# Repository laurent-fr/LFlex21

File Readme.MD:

# LFlex21, a single board 6809/Flex computer

   * 6809 CPU
   * 58Kb RAM
   * 4Kb ROM
   * 2Kb NVRAM
   * RTC clock
   * Serial interface up to 9600 bauds
   * Centronic printer port
   * floppy controller
   * FLEX09 operating system

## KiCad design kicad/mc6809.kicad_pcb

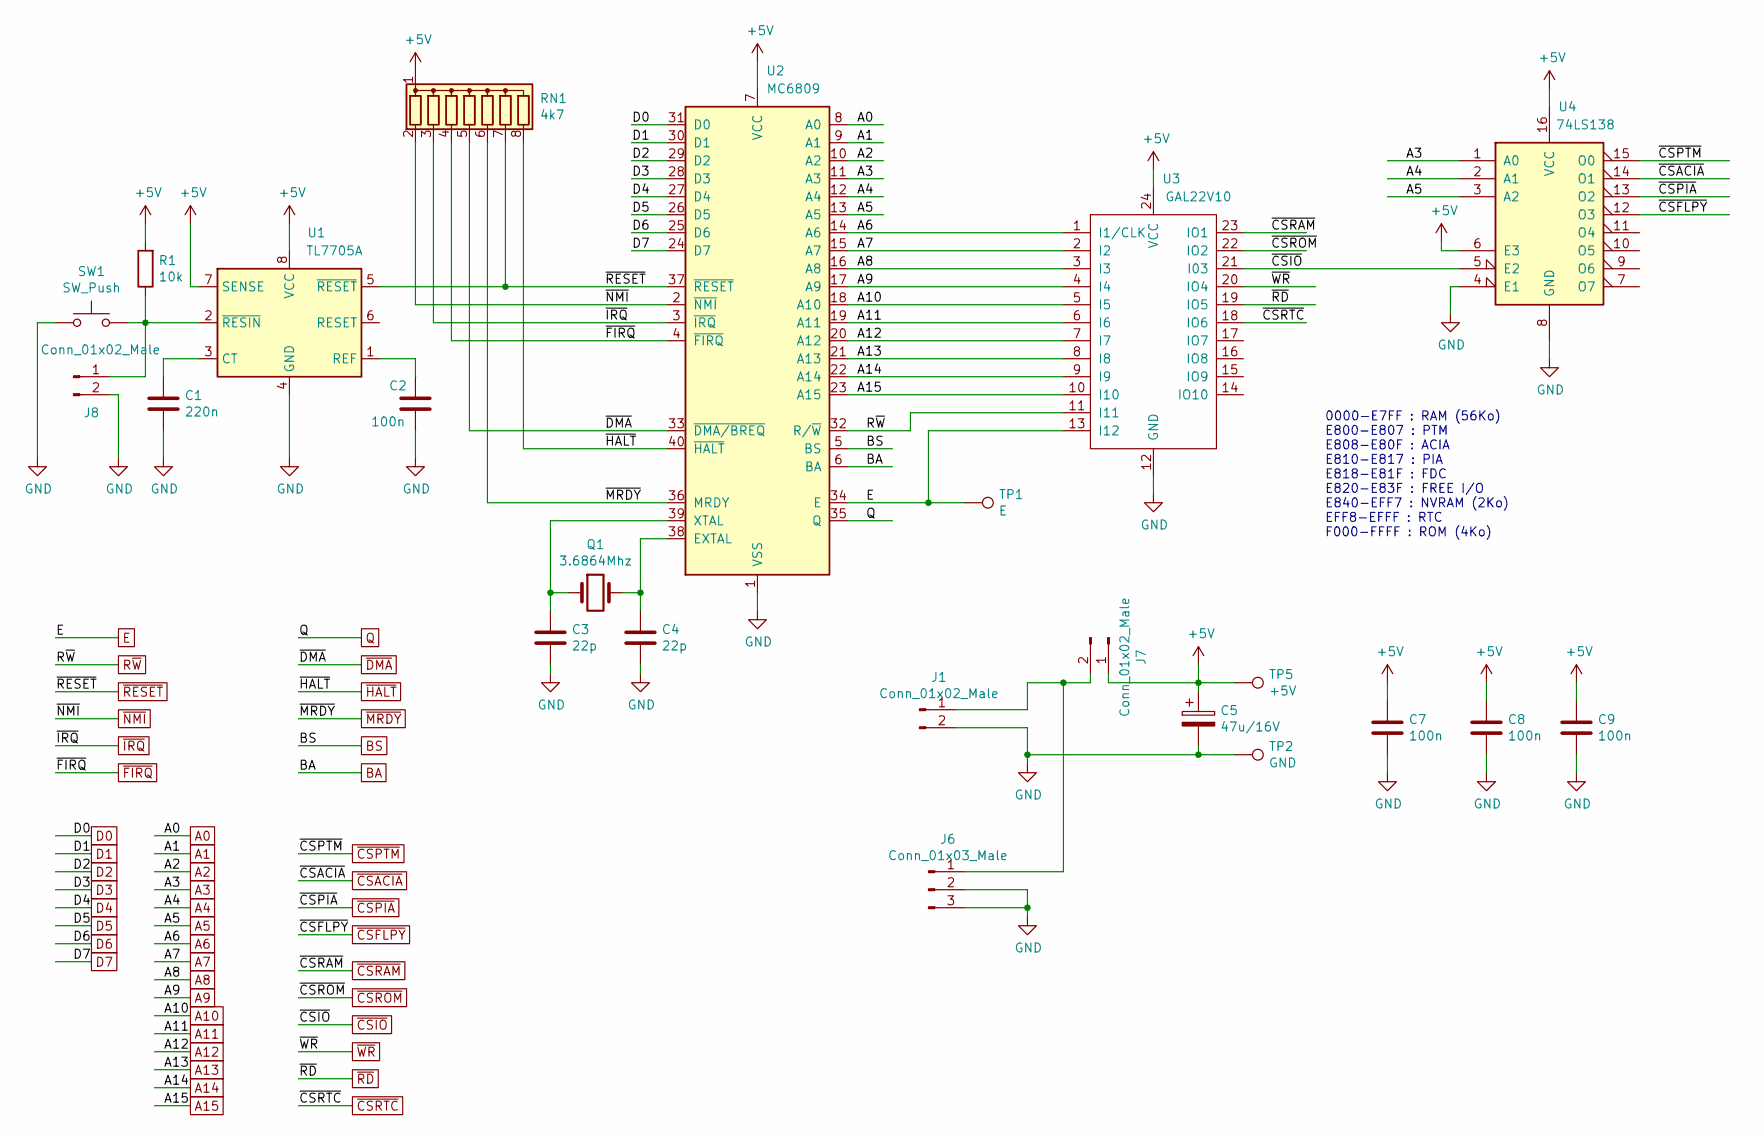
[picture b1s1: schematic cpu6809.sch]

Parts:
C1: 220n; C_Disc_D4.3mm_W1.9mm_P5.00mm
C2, C7, C8, C9: 100n; C_Disc_D4.3mm_W1.9mm_P5.00mm
C3, C4: 22p; C_Disc_D3.0mm_W1.6mm_P2.50mm
C5: 47u/16V; CP_Radial_D5.0mm_P2.50mm
J1: Conn_01x02_Male; JACK_ALIM
J6: Conn_01x03_Male; Molex_KK-6410-03_03x2.54mm_Straight
J7: Conn_01x02_Male; Molex_KK-6410-02_02x2.54mm_Straight
J8: Conn_01x02_Male; Pin_Header_Straight_1x02_Pitch2.54mm
Q1: 3.6864Mhz; Crystal_HC18-U_Vertical
R1: 10k; R_Axial_DIN0207_L6.3mm_D2.5mm_P7.62mm_Horizontal
RN1: 4k7; R_Array_SIP8
SW1: SW_Push; SW_PUSH_6mm
TP1: E; Pin_d1.0mm_L10.0mm
TP2: GND; Pin_d1.0mm_L10.0mm
TP5: +5V; Pin_d1.0mm_L10.0mm
U1: TL7705A; DIP-8_W7.62mm_LongPads
U2: MC6809; DIP-40_W15.24mm_LongPads
U3: GAL22V10; DIP-24_W7.62mm_LongPads
U4: 74LS138; DIP-16_W7.62mm_LongPads

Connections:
+5V: C5.1, C7.1, C8.1, C9.1, J7.1, R1.2, RN1.1 (common), TP5.1, U1.7 (SENSE), U1.8 (VCC), U2.7 (VCC), U3.24 (VCC), U4.6 (E3), U4.16 (VCC); also elsewhere on the board
A0: U2.8 (A0); also elsewhere on the board
A1: U2.9 (A1); also elsewhere on the board
A2: U2.10 (A2); also elsewhere on the board
A3: U2.11 (A3), U4.1 (A0); also elsewhere on the board
A4: U2.12 (A4), U4.2 (A1); also elsewhere on the board
A5: U2.13 (A5), U4.3 (A2); also elsewhere on the board
A6: U2.14 (A6), U3.1 (I1/CLK); also elsewhere on the board
A7: U2.15 (A7), U3.2 (I2); also elsewhere on the board
A8: U2.16 (A8), U3.3 (I3); also elsewhere on the board
A9: U2.17 (A9), U3.4 (I4); also elsewhere on the board
A10: U2.18 (A10), U3.5 (I5); also elsewhere on the board
A11: U2.19 (A11), U3.6 (I6); also elsewhere on the board
A12: U2.20 (A12), U3.7 (I7); also elsewhere on the board
A13: U2.21 (A13), U3.8 (I8); also elsewhere on the board
A14: U2.22 (A14), U3.9 (I9); also elsewhere on the board
A15: U2.23 (A15), U3.10 (I10); also elsewhere on the board
BA: U2.6 (BA); also elsewhere on the board
BS: U2.5 (BS); also elsewhere on the board
D0: U2.31 (D0); also elsewhere on the board
D1: U2.30 (D1); also elsewhere on the board
D2: U2.29 (D2); also elsewhere on the board
D3: U2.28 (D3); also elsewhere on the board
D4: U2.27 (D4); also elsewhere on the board
D5: U2.26 (D5); also elsewhere on the board
D6: U2.25 (D6); also elsewhere on the board
D7: U2.24 (D7); also elsewhere on the board
E: TP1.1, U2.34 (E), U3.13 (I12); also elsewhere on the board
GND: C1.2, C2.2, C3.2, C4.2, C5.2, C7.2, C8.2, C9.2, J1.2, J6.2, J6.3, J8.2, SW1.1, TP2.1, U1.4 (GND), U2.1 (VSS), U3.12 (GND), U4.4 (E1), U4.8 (GND); also elsewhere on the board
unnamed: C1.1, U1.3 (CT)
unnamed: C2.1, U1.1 (REF)
unnamed: C3.1, Q1.1, U2.39 (XTAL)
unnamed: C4.1, Q1.2, U2.38 (EXTAL)
unnamed: J1.1, J6.1, J7.2
unnamed: J8.1, R1.1, SW1.2, U1.2 (~RESIN)
Q: U2.35 (Q); also elsewhere on the board
R~W~: U2.32 (R/~W), U3.11 (I11); also elsewhere on the board
~CSACIA~: U4.14 (O1); also elsewhere on the board
~CSFLPY~: U4.12 (O3); also elsewhere on the board
~CSIO~: U3.21 (I03), U4.5 (E2); also elsewhere on the board
~CSPIA~: U4.13 (O2); also elsewhere on the board
~CSPTM~: U4.15 (O0); also elsewhere on the board
~CSRAM~: U3.23 (IO1); also elsewhere on the board
~CSROM~: U3.22 (IO2); also elsewhere on the board
~CSRTC~: U3.18 (IO6); also elsewhere on the board
~DMA~: RN1.5 (R4), U2.33 (~DMA/BREQ); also elsewhere on the board
~FIRQ~: RN1.4 (R3), U2.4 (~FIRQ); also elsewhere on the board
~HALT~: RN1.8 (R7), U2.40 (~HALT); also elsewhere on the board
~IRQ~: RN1.3 (R2), U2.3 (~IRQ); also elsewhere on the board
~MRDY~: RN1.6 (R5), U2.36 (MRDY); also elsewhere on the board
~NMI~: RN1.2 (R1), U2.2 (~NMI); also elsewhere on the board
~RD~: U3.19 (IO5); also elsewhere on the board
~RESET~: RN1.7 (R6), U1.5 (~RESET), U2.37 (~RESET); also elsewhere on the board
~WR~: U3.20 (IO4); also elsewhere on the board

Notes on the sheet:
0000-E7FF : RAM (56Ko) E800-E807 : PTM E808-E80F : ACIA E810-E817 : PIA E818-E81F : FDC E820-E83F : FREE I/O E840-EFF7 : NVRAM (2Ko) EFF8-EFFF : RTC F000-FFFF : ROM (4Ko)

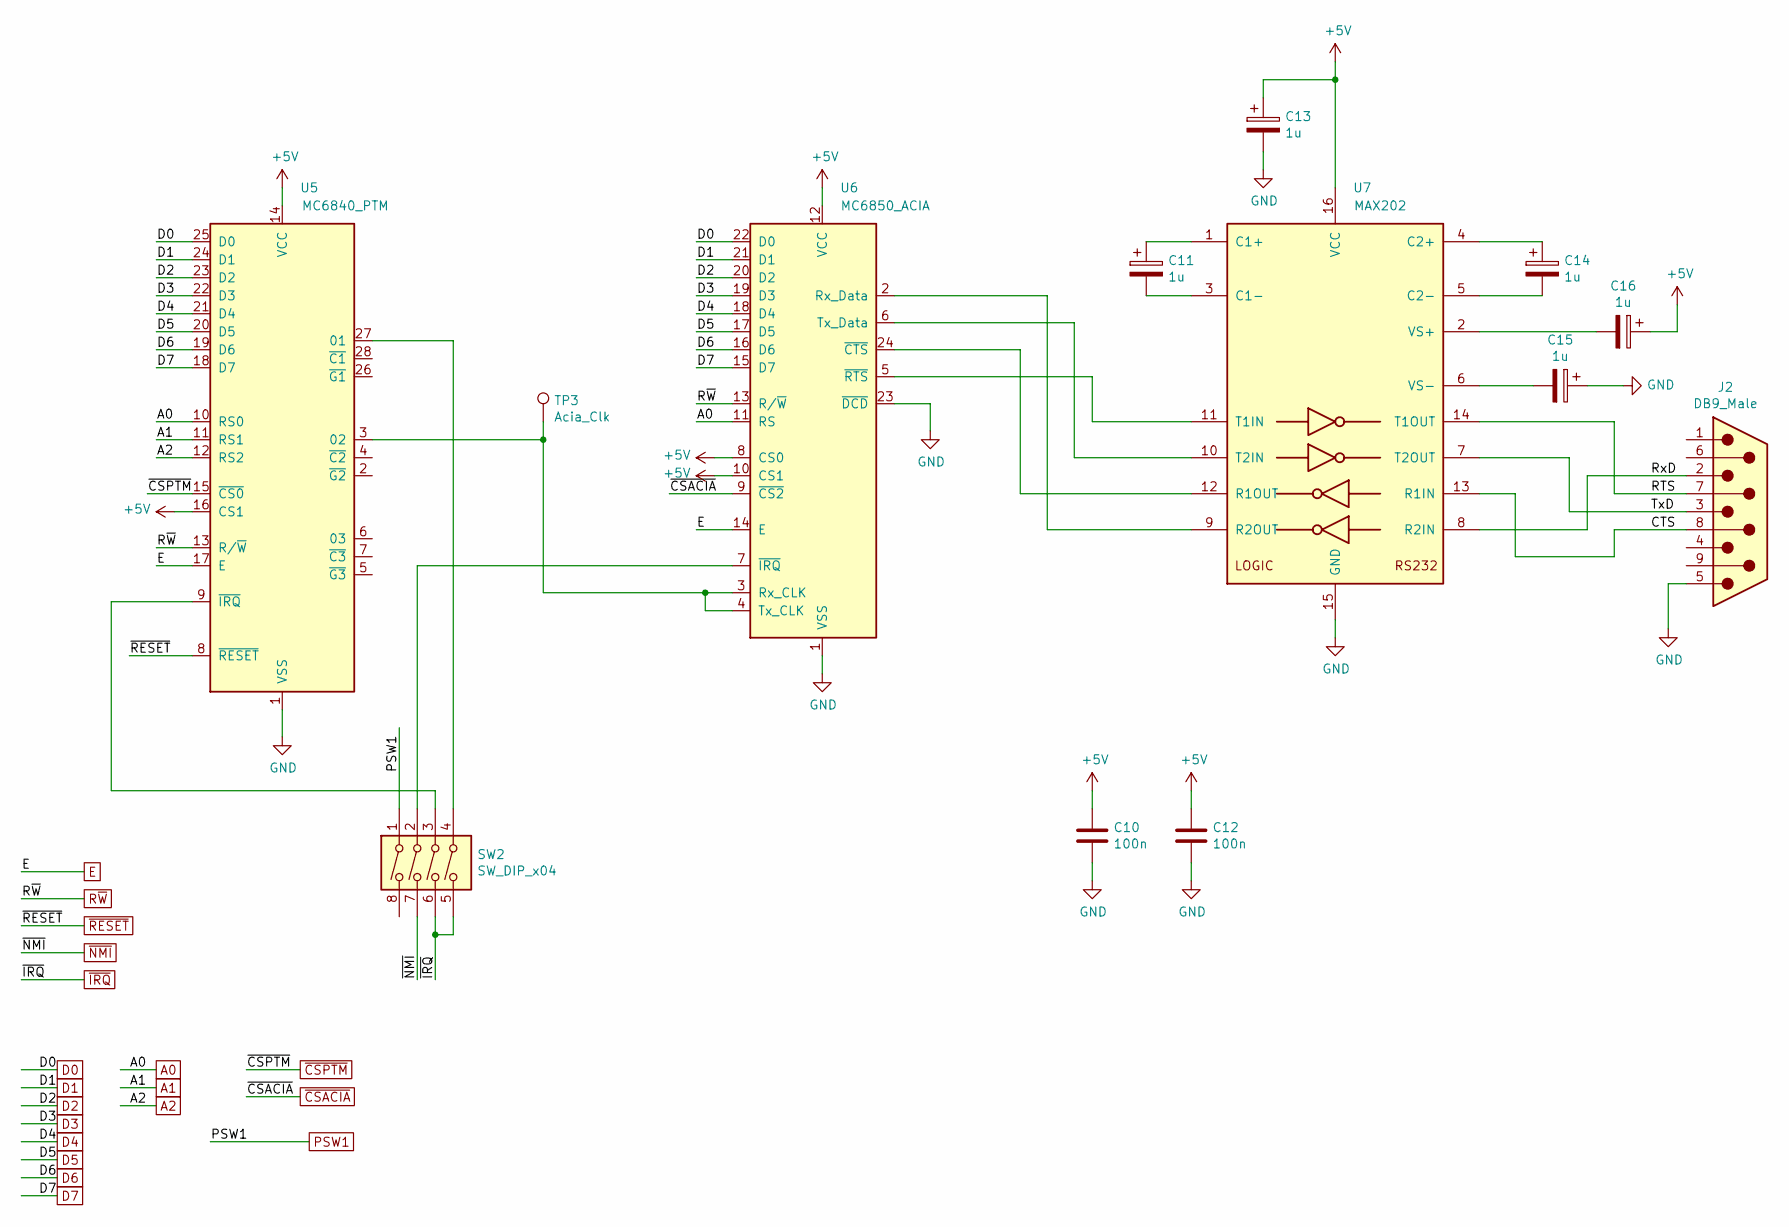
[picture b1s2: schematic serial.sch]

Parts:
C10, C12: 100n; C_Disc_D4.3mm_W1.9mm_P5.00mm
C11, C13, C14, C15, C16: 1u; CP_Radial_D5.0mm_P2.50mm
J2: DB9_Male; DSUB-9_Male_Horizontal_Pitch2.77x2.84mm_EdgePinOffset7.70mm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
SW2: SW_DIP_x04; SW_DIP_x4_W7.62mm_Slide
TP3: Acia_Clk; Pin_d1.0mm_L10.0mm
U5: MC6840_PTM; DIP-28_W15.24mm_LongPads
U6: MC6850_ACIA; DIP-24_W15.24mm_LongPads
U7: MAX202; DIP-16_W7.62mm_LongPads

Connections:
+5V: C10.1, C12.1, C13.1, C16.1, U5.14 (VCC), U5.16 (CS1), U6.8 (CS0), U6.10 (CS1), U6.12 (VCC), U7.16 (VCC); also elsewhere on the board
/serial/CTS: J2.8, U7.13 (R1IN)
/serial/RTS: J2.7, U7.14 (T1OUT)
/serial/RxD: J2.2, U7.8 (R2IN)
/serial/TxD: J2.3, U7.7 (T2OUT)
A0: U5.10 (RS0), U6.11 (RS); also elsewhere on the board
A1: U5.11 (RS1); also elsewhere on the board
A2: U5.12 (RS2); also elsewhere on the board
D0: U5.25 (D0), U6.22 (D0); also elsewhere on the board
D1: U5.24 (D1), U6.21 (D1); also elsewhere on the board
D2: U5.23 (D2), U6.20 (D2); also elsewhere on the board
D3: U5.22 (D3), U6.19 (D3); also elsewhere on the board
D4: U5.21 (D4), U6.18 (D4); also elsewhere on the board
D5: U5.20 (D5), U6.17 (D5); also elsewhere on the board
D6: U5.19 (D6), U6.16 (D6); also elsewhere on the board
D7: U5.18 (D7), U6.15 (D7); also elsewhere on the board
E: U5.17 (E), U6.14 (E); also elsewhere on the board
GND: C10.2, C12.2, C13.2, C15.1, J2.5, U5.1 (VSS), U6.1 (VSS), U6.23 (~DCD), U7.15 (GND); also elsewhere on the board
unnamed: C11.1, U7.1 (C1+)
unnamed: C11.2, U7.3 (C1-)
unnamed: C14.1, U7.4 (C2+)
unnamed: C14.2, U7.5 (C2-)
unnamed: C15.2, U7.6 (VS-)
unnamed: C16.2, U7.2 (VS+)
unnamed: SW2.2, U6.7 (~IRQ)
unnamed: SW2.3, U5.9 (~IRQ)
unnamed: SW2.4, U5.27 (01)
unnamed: TP3.1, U5.3 (02), U6.3 (Rx_CLK), U6.4 (Tx_CLK)
unnamed: U6.2 (Rx_Data), U7.9 (R2OUT)
unnamed: U6.5 (~RTS), U7.11 (T1IN)
unnamed: U6.6 (Tx_Data), U7.10 (T2IN)
unnamed: U6.24 (~CTS), U7.12 (R1OUT)
PSW1: SW2.1; also elsewhere on the board
R~W~: U5.13 (R/~W), U6.13 (R/~W); also elsewhere on the board
~CSACIA~: U6.9 (~CS2~); also elsewhere on the board
~CSPTM~: U5.15 (~CS0~); also elsewhere on the board
~IRQ~: SW2.5, SW2.6; also elsewhere on the board
~NMI~: SW2.7; also elsewhere on the board
~RESET~: U5.8 (~RESET); also elsewhere on the board

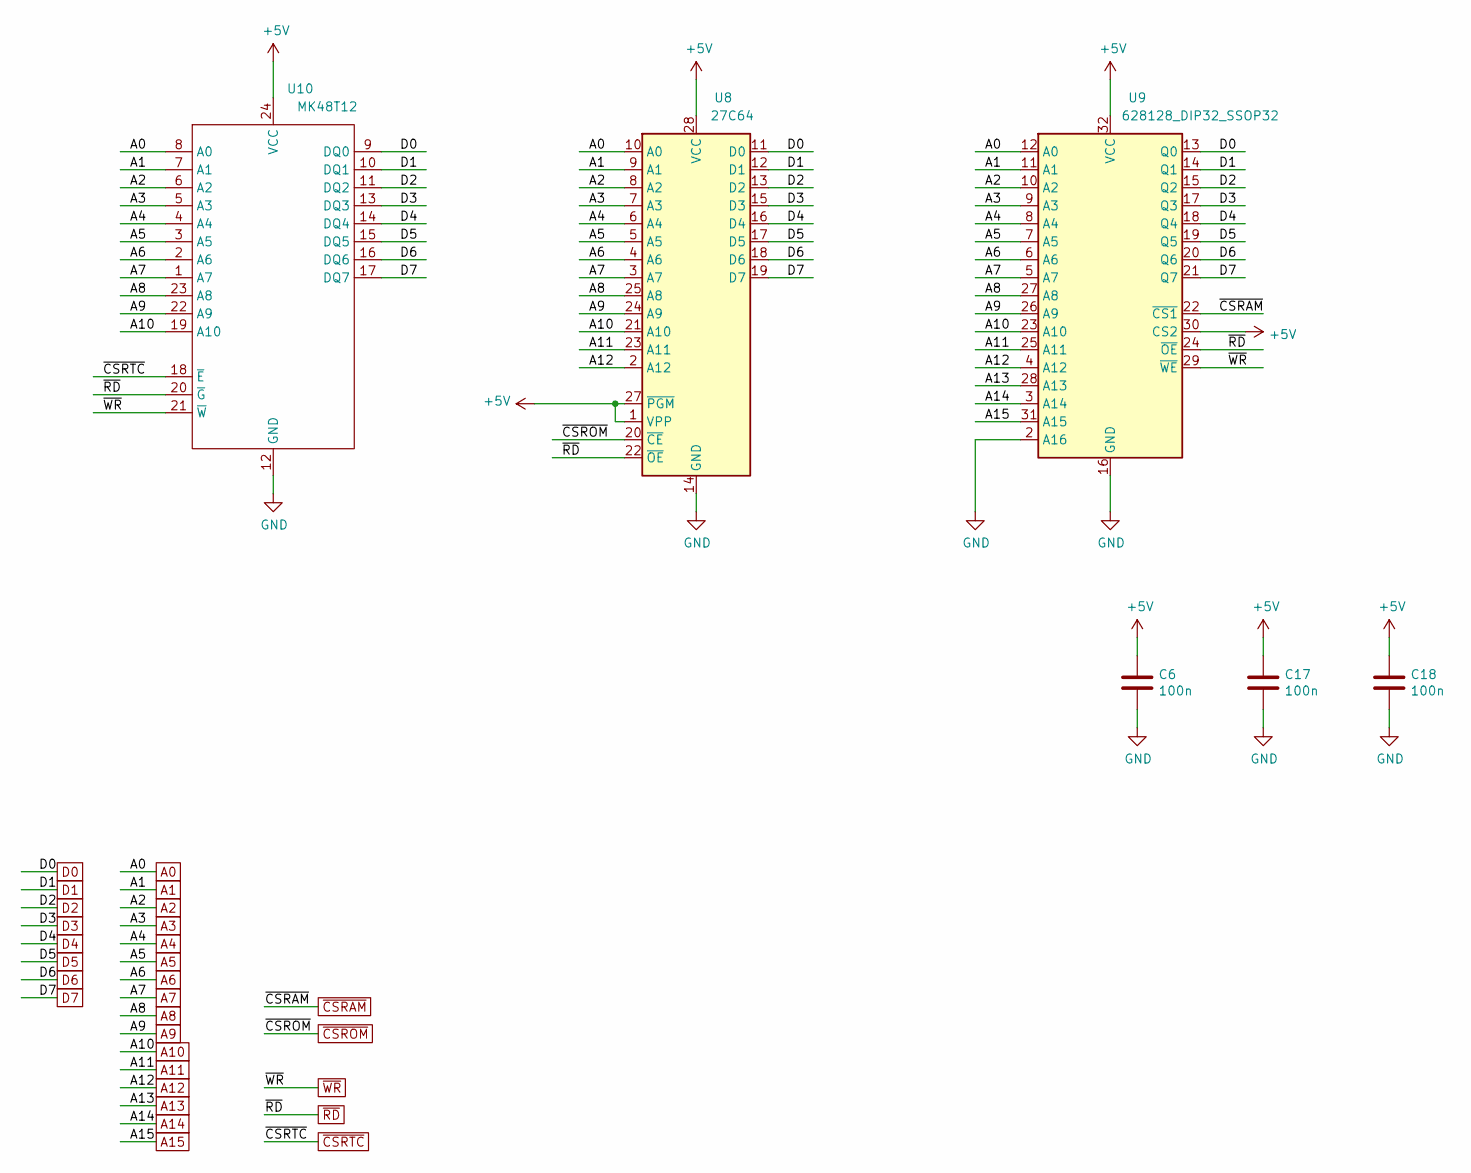
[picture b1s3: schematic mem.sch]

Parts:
C6, C17, C18: 100n; C_Disc_D4.3mm_W1.9mm_P5.00mm
U8: 27C64; DIP-28_W15.24mm_LongPads
U9: 628128_DIP32_SSOP32; DIP-32_W15.24mm_LongPads
U10: MK48T12; DIP-24_W15.24mm_LongPads

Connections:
+5V: C6.1, C17.1, C18.1, U8.1 (VPP), U8.27 (~PGM), U8.28 (VCC), U9.30 (CS2), U9.32 (VCC), U10.24 (VCC); also elsewhere on the board
A0: U8.10 (A0), U9.12 (A0), U10.8 (A0); also elsewhere on the board
A1: U8.9 (A1), U9.11 (A1), U10.7 (A1); also elsewhere on the board
A2: U8.8 (A2), U9.10 (A2), U10.6 (A2); also elsewhere on the board
A3: U8.7 (A3), U9.9 (A3), U10.5 (A3); also elsewhere on the board
A4: U8.6 (A4), U9.8 (A4), U10.4 (A4); also elsewhere on the board
A5: U8.5 (A5), U9.7 (A5), U10.3 (A5); also elsewhere on the board
A6: U8.4 (A6), U9.6 (A6), U10.2 (A6); also elsewhere on the board
A7: U8.3 (A7), U9.5 (A7), U10.1 (A7); also elsewhere on the board
A8: U8.25 (A8), U9.27 (A8), U10.23 (A8); also elsewhere on the board
A9: U8.24 (A9), U9.26 (A9), U10.22 (A9); also elsewhere on the board
A10: U8.21 (A10), U9.23 (A10), U10.19 (A10); also elsewhere on the board
A11: U8.23 (A11), U9.25 (A11); also elsewhere on the board
A12: U8.2 (A12), U9.4 (A12); also elsewhere on the board
A13: U9.28 (A13); also elsewhere on the board
A14: U9.3 (A14); also elsewhere on the board
A15: U9.31 (A15); also elsewhere on the board
D0: U8.11 (D0), U9.13 (Q0), U10.9 (DQ0); also elsewhere on the board
D1: U8.12 (D1), U9.14 (Q1), U10.10 (DQ1); also elsewhere on the board
D2: U8.13 (D2), U9.15 (Q2), U10.11 (DQ2); also elsewhere on the board
D3: U8.15 (D3), U9.17 (Q3), U10.13 (DQ3); also elsewhere on the board
D4: U8.16 (D4), U9.18 (Q4), U10.14 (DQ4); also elsewhere on the board
D5: U8.17 (D5), U9.19 (Q5), U10.15 (DQ5); also elsewhere on the board
D6: U8.18 (D6), U9.20 (Q6), U10.16 (DQ6); also elsewhere on the board
D7: U8.19 (D7), U9.21 (Q7), U10.17 (DQ7); also elsewhere on the board
GND: C6.2, C17.2, C18.2, U8.14 (GND), U9.2 (A16), U9.16 (GND), U10.12 (GND); also elsewhere on the board
~CSRAM~: U9.22 (~CS1); also elsewhere on the board
~CSROM~: U8.20 (~CE); also elsewhere on the board
~CSRTC~: U10.18 (~E~); also elsewhere on the board
~RD~: U8.22 (~OE), U9.24 (~OE), U10.20 (~G~); also elsewhere on the board
~WR~: U9.29 (~WE), U10.21 (~W~); also elsewhere on the board

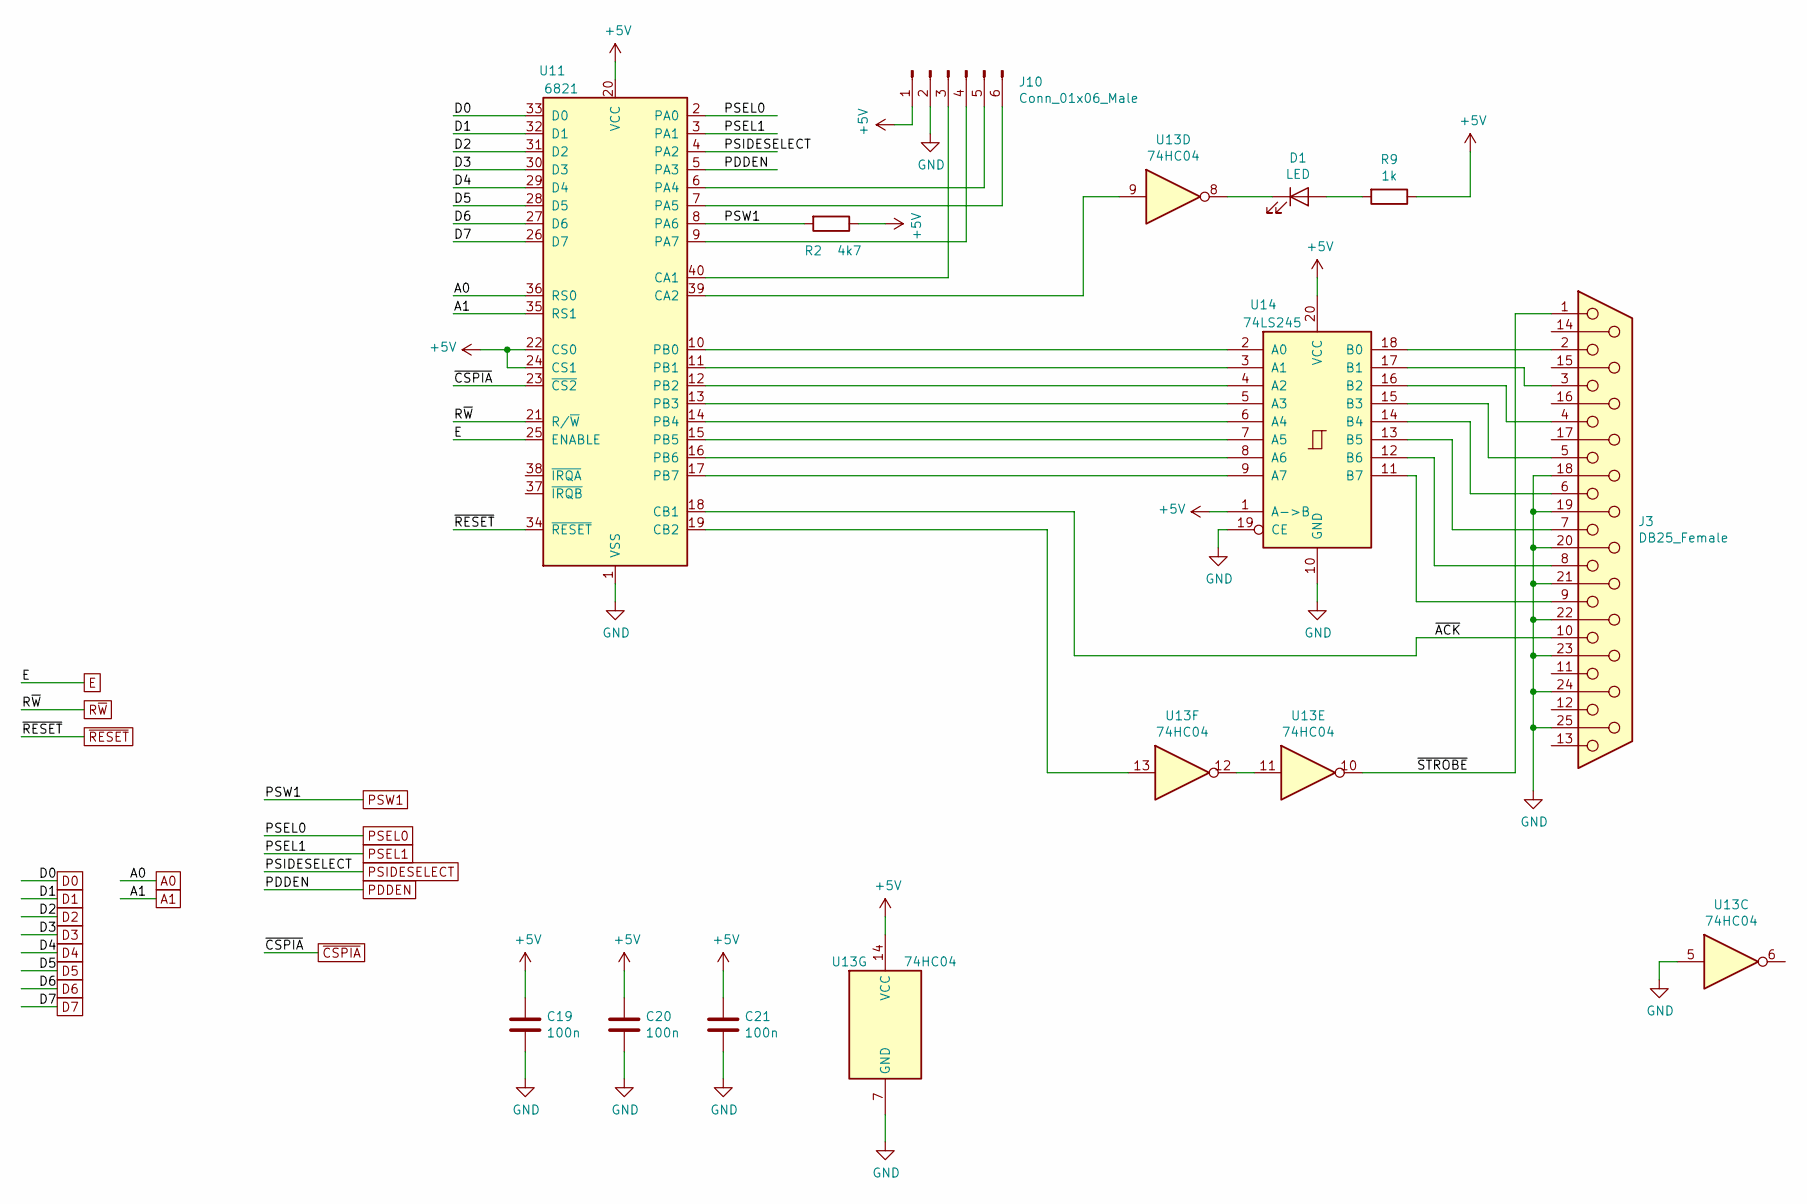
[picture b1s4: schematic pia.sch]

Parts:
C19, C20, C21: 100n; C_Disc_D4.3mm_W1.9mm_P5.00mm
D1: LED; LED_D3.0mm
J3: DB25_Female; DSUB-25_Female_Horizontal_Pitch2.77x2.84mm_EdgePinOffset7.7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
J10: Conn_01x06_Male; Pin_Header_Straight_1x06_Pitch2.54mm
R2: 4k7; R_Axial_DIN0207_L6.3mm_D2.5mm_P7.62mm_Horizontal
R9: 1k; R_Axial_DIN0207_L6.3mm_D2.5mm_P7.62mm_Horizontal
U11: 6821; DIP-40_W15.24mm_LongPads
U13: 74HC04; DIP-14_W7.62mm_LongPads
U14: 74LS245; DIP-20_W7.62mm_LongPads

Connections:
+5V: C19.1, C20.1, C21.1, J10.1, R2.1, R9.1, U11.20 (VCC), U11.22 (CS0), U11.24 (CS1), U13.14 (VCC), U14.1 (A->B), U14.20 (VCC); also elsewhere on the board
/pia/~ACK~: J3.10, U11.18 (CB1)
/pia/~STROBE~: J3.1, U13.10
A0: U11.36 (RS0); also elsewhere on the board
A1: U11.35 (RS1); also elsewhere on the board
D0: U11.33 (D0); also elsewhere on the board
D1: U11.32 (D1); also elsewhere on the board
D2: U11.31 (D2); also elsewhere on the board
D3: U11.30 (D3); also elsewhere on the board
D4: U11.29 (D4); also elsewhere on the board
D5: U11.28 (D5); also elsewhere on the board
D6: U11.27 (D6); also elsewhere on the board
D7: U11.26 (D7); also elsewhere on the board
E: U11.25 (ENABLE); also elsewhere on the board
GND: C19.2, C20.2, C21.2, J3.18, J3.19, J3.20, J3.21, J3.22, J3.23, J3.24, J3.25, J10.2, U11.1 (VSS), U13.5, U13.7 (GND), U14.10 (GND), U14.19 (CE); also elsewhere on the board
unnamed: D1.1 (K), U13.8
unnamed: D1.2 (A), R9.2
unnamed: J3.2, U14.18 (B0)
unnamed: J3.3, U14.17 (B1)
unnamed: J3.4, U14.16 (B2)
unnamed: J3.5, U14.15 (B3)
unnamed: J3.6, U14.14 (B4)
unnamed: J3.7, U14.13 (B5)
unnamed: J3.8, U14.12 (B6)
unnamed: J3.9, U14.11 (B7)
unnamed: J10.3, U11.40 (CA1)
unnamed: J10.4, U11.9 (PA7)
unnamed: J10.5, U11.6 (PA4)
unnamed: J10.6, U11.7 (PA5)
unnamed: U11.10 (PB0), U14.2 (A0)
unnamed: U11.11 (PB1), U14.3 (A1)
unnamed: U11.12 (PB2), U14.4 (A2)
unnamed: U11.13 (PB3), U14.5 (A3)
unnamed: U11.14 (PB4), U14.6 (A4)
unnamed: U11.15 (PB5), U14.7 (A5)
unnamed: U11.16 (PB6), U14.8 (A6)
unnamed: U11.17 (PB7), U14.9 (A7)
unnamed: U11.19 (CB2), U13.13
unnamed: U11.39 (CA2), U13.9
unnamed: U13.11, U13.12
PDDEN: U11.5 (PA3); also elsewhere on the board
PSEL0: U11.2 (PA0); also elsewhere on the board
PSEL1: U11.3 (PA1); also elsewhere on the board
PSIDESELECT: U11.4 (PA2); also elsewhere on the board
PSW1: R2.2, U11.8 (PA6); also elsewhere on the board
R~W~: U11.21 (R/~W); also elsewhere on the board
~CSPIA~: U11.23 (~CS2); also elsewhere on the board
~RESET~: U11.34 (~RESET); also elsewhere on the board

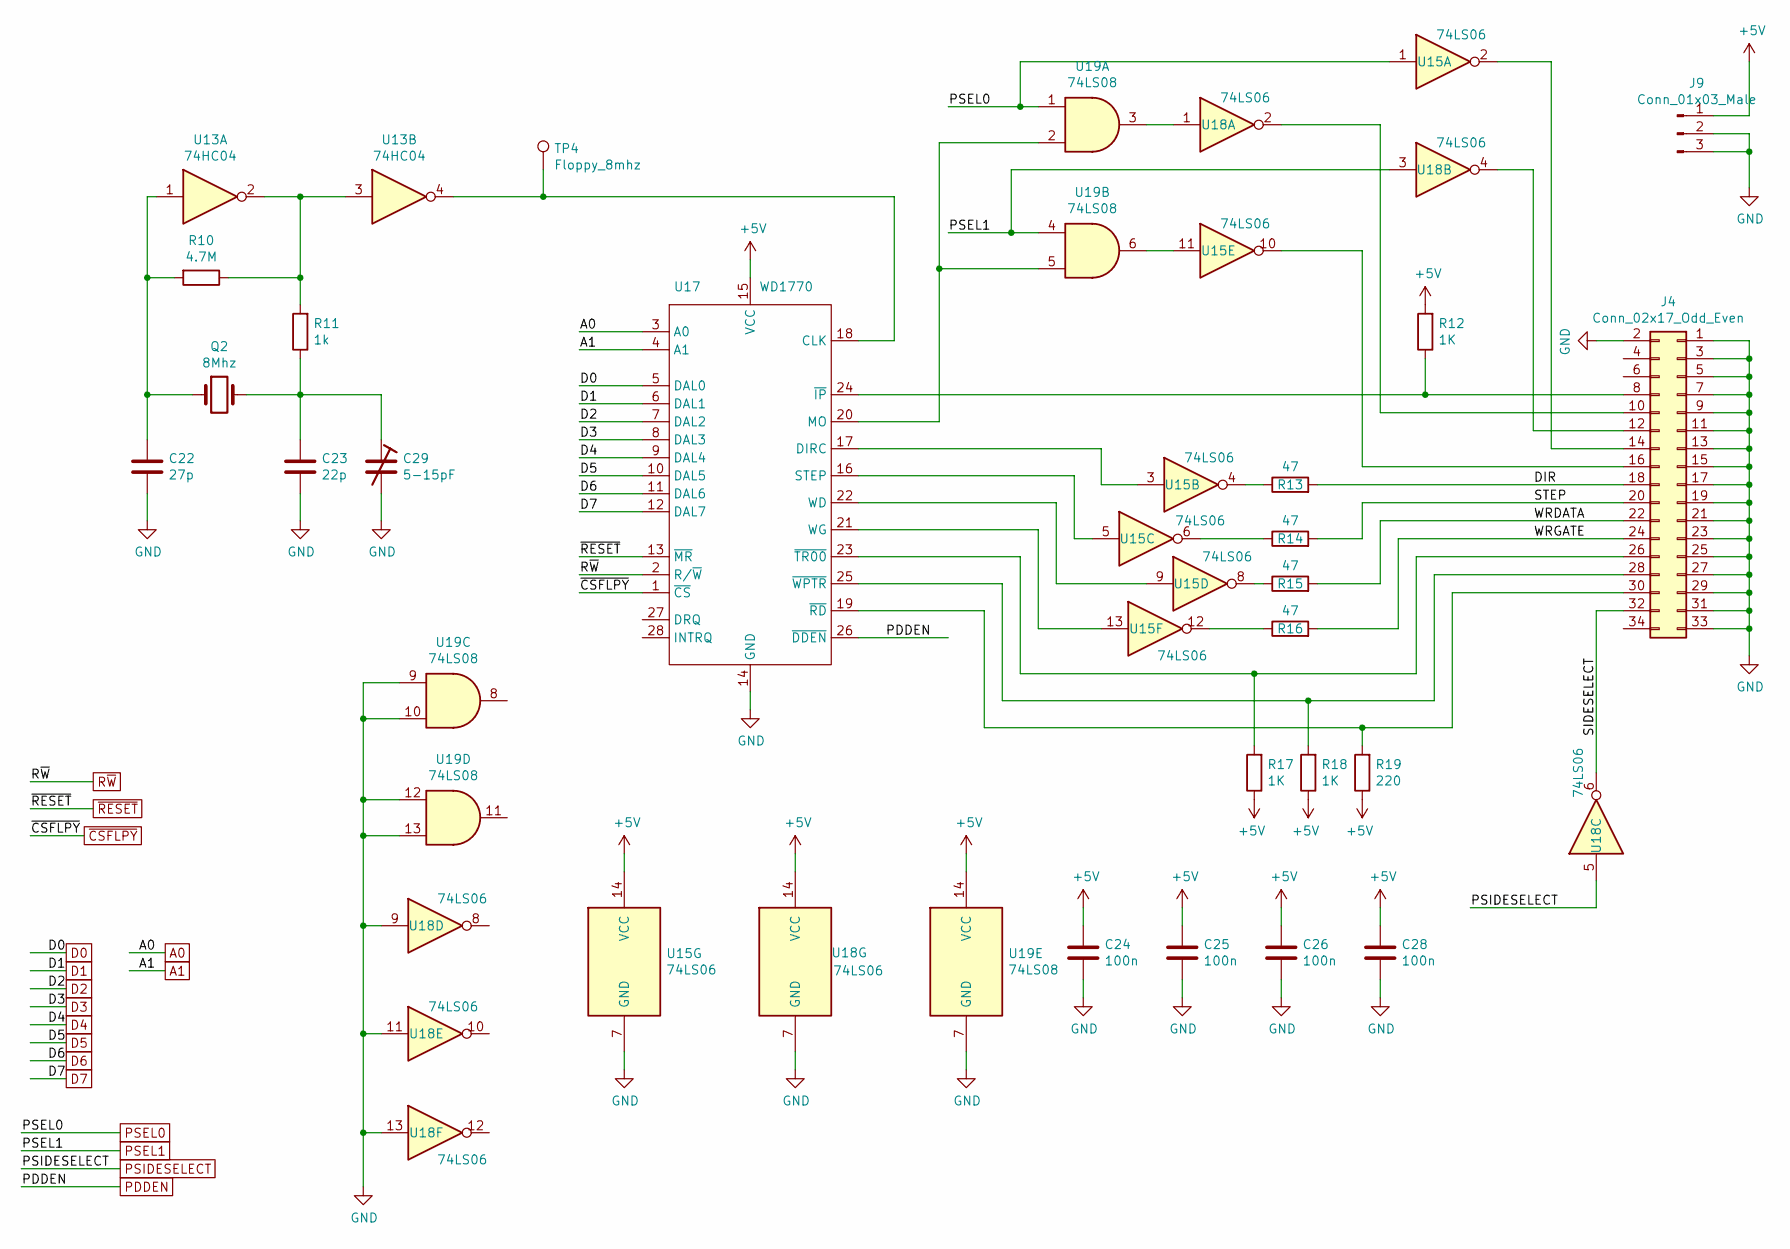
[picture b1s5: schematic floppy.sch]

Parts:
C22: 27p; C_Disc_D3.0mm_W1.6mm_P2.50mm
C23: 22p; C_Disc_D3.0mm_W1.6mm_P2.50mm
C24, C25, C26, C28: 100n; C_Disc_D4.3mm_W1.9mm_P5.00mm
C29: 5-15pF; C-TRIMMER-5
J4: Conn_02x17_Odd_Even; Multicomp_MC9A12-3434_2x17x2.54mm_Straight
J9: Conn_01x03_Male; Molex_KK-6410-03_03x2.54mm_Straight
Q2: 8Mhz; Crystal_HC18-U_Vertical
R10: 4.7M; R_Axial_DIN0207_L6.3mm_D2.5mm_P7.62mm_Horizontal
R11: 1k; R_Axial_DIN0207_L6.3mm_D2.5mm_P7.62mm_Horizontal
R12, R17, R18: 1K; R_Axial_DIN0204_L3.6mm_D1.6mm_P7.62mm_Horizontal
R13, R14, R15, R16: 47; R_Axial_DIN0204_L3.6mm_D1.6mm_P7.62mm_Horizontal
R19: 220; R_Axial_DIN0204_L3.6mm_D1.6mm_P7.62mm_Horizontal
TP4: Floppy_8mhz; Pin_d1.0mm_L10.0mm
U13: 74HC04; DIP-14_W7.62mm_LongPads
U15, U18: 74LS06; DIP-14_W7.62mm_LongPads
U17: WD1770; DIP-28_W15.24mm_LongPads
U19: 74LS08; DIP-14_W7.62mm_LongPads

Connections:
+5V: C24.1, C25.1, C26.1, C28.1, J9.1, R12.2, R17.1, R18.1, R19.1, U15.14 (VCC), U17.15 (VCC), U18.14 (VCC), U19.14 (VCC); also elsewhere on the board
/floppy/DIR: J4.18, R13.2
/floppy/SIDESELECT: J4.32, U18.6
/floppy/STEP: J4.20, R14.2
/floppy/WRDATA: J4.22, R15.2
/floppy/WRGATE: J4.24, R16.2
A0: U17.3 (A0); also elsewhere on the board
A1: U17.4 (A1); also elsewhere on the board
D0: U17.5 (DAL0); also elsewhere on the board
D1: U17.6 (DAL1); also elsewhere on the board
D2: U17.7 (DAL2); also elsewhere on the board
D3: U17.8 (DAL3); also elsewhere on the board
D4: U17.9 (DAL4); also elsewhere on the board
D5: U17.10 (DAL5); also elsewhere on the board
D6: U17.11 (DAL6); also elsewhere on the board
D7: U17.12 (DAL7); also elsewhere on the board
GND: C22.2, C23.2, C24.2, C25.2, C26.2, C28.2, C29.2, J4.1, J4.2, J4.3, J4.5, J4.7, J4.9, J4.11, J4.13, J4.15, J4.17, J4.19, J4.21, J4.23, J4.25, J4.27, J4.29, J4.31, J4.33, J9.2, J9.3, U15.7 (GND), U17.14 (GND), U18.7 (GND), U18.9, U18.11, U18.13, U19.7 (GND), U19.9, U19.10, U19.12, U19.13; also elsewhere on the board
unnamed: C22.1, Q2.1, R10.2, U13.1
unnamed: C23.1, C29.1, Q2.2, R11.1
unnamed: J4.8, R12.1, U17.24 (~IP~)
unnamed: J4.10, U18.2
unnamed: J4.12, U18.4
unnamed: J4.14, U15.2
unnamed: J4.16, U15.10
unnamed: J4.26, R17.2, U17.23 (~TR00~)
unnamed: J4.28, R18.2, U17.25 (~WPTR~)
unnamed: J4.30, R19.2, U17.19 (~RD~)
unnamed: R10.1, R11.2, U13.2, U13.3
unnamed: R13.1, U15.4
unnamed: R14.1, U15.6
unnamed: R15.1, U15.8
unnamed: R16.1, U15.12
unnamed: TP4.1, U13.4, U17.18 (CLK)
unnamed: U15.3, U17.17 (DIRC)
unnamed: U15.5, U17.16 (STEP)
unnamed: U15.9, U17.22 (WD)
unnamed: U15.11, U19.6
unnamed: U15.13, U17.21 (WG)
unnamed: U17.20 (MO), U19.2, U19.5
unnamed: U18.1, U19.3
PDDEN: U17.26 (~DDEN~); also elsewhere on the board
PSEL0: U15.1, U19.1; also elsewhere on the board
PSEL1: U18.3, U19.4; also elsewhere on the board
PSIDESELECT: U18.5; also elsewhere on the board
R~W~: U17.2 (R/~W~); also elsewhere on the board
~CSFLPY~: U17.1 (~CS~); also elsewhere on the board
~RESET~: U17.13 (~MR~); also elsewhere on the board

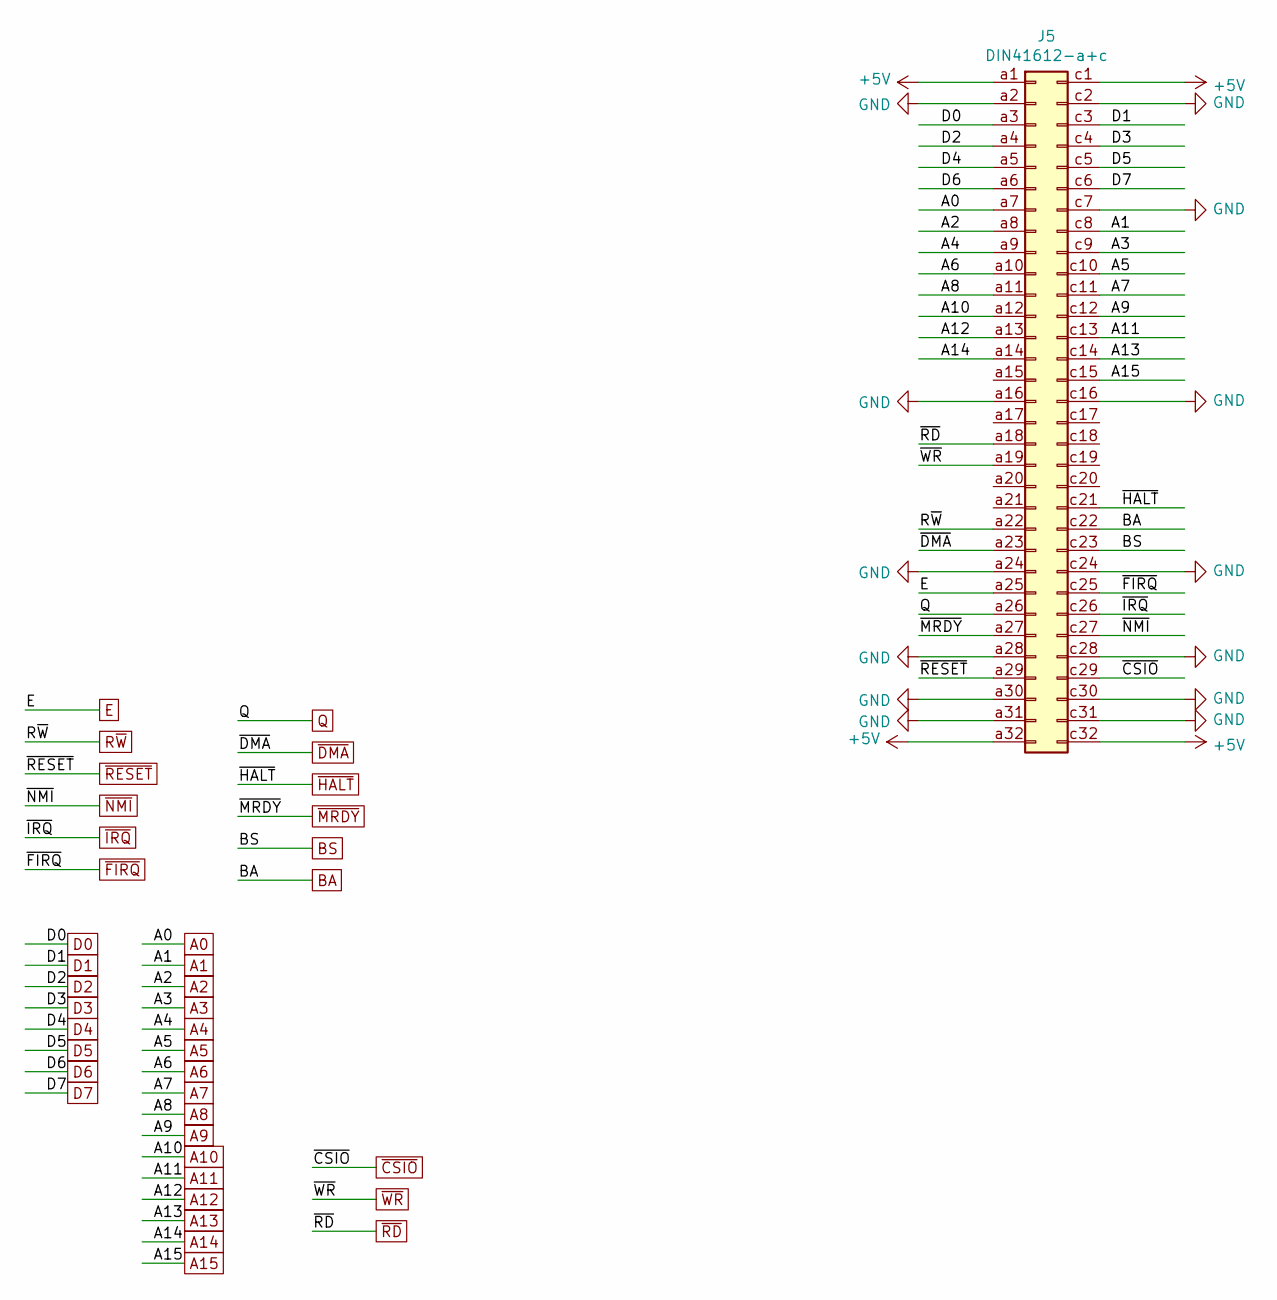
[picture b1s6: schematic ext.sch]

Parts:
J5: DIN41612-a+c; Socket_DIN41612-CaseC1-AC-Male-64Pin-2rows-nosilk

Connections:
+5V: J5.a1, J5.a32, J5.c1, J5.c32; also elsewhere on the board
A0: J5.a7; also elsewhere on the board
A1: J5.c8; also elsewhere on the board
A2: J5.a8; also elsewhere on the board
A3: J5.c9; also elsewhere on the board
A4: J5.a9; also elsewhere on the board
A5: J5.c10; also elsewhere on the board
A6: J5.a10; also elsewhere on the board
A7: J5.c11; also elsewhere on the board
A8: J5.a11; also elsewhere on the board
A9: J5.c12; also elsewhere on the board
A10: J5.a12; also elsewhere on the board
A11: J5.c13; also elsewhere on the board
A12: J5.a13; also elsewhere on the board
A13: J5.c14; also elsewhere on the board
A14: J5.a14; also elsewhere on the board
A15: J5.c15; also elsewhere on the board
BA: J5.c22; also elsewhere on the board
BS: J5.c23; also elsewhere on the board
D0: J5.a3; also elsewhere on the board
D1: J5.c3; also elsewhere on the board
D2: J5.a4; also elsewhere on the board
D3: J5.c4; also elsewhere on the board
D4: J5.a5; also elsewhere on the board
D5: J5.c5; also elsewhere on the board
D6: J5.a6; also elsewhere on the board
D7: J5.c6; also elsewhere on the board
E: J5.a25; also elsewhere on the board
GND: J5.a2, J5.a16, J5.a24, J5.a28, J5.a30, J5.a31, J5.c2, J5.c7, J5.c16, J5.c24, J5.c28, J5.c30, J5.c31; also elsewhere on the board
Q: J5.a26; also elsewhere on the board
R~W~: J5.a22; also elsewhere on the board
~CSIO~: J5.c29; also elsewhere on the board
~DMA~: J5.a23; also elsewhere on the board
~FIRQ~: J5.c25; also elsewhere on the board
~HALT~: J5.c21; also elsewhere on the board
~IRQ~: J5.c26; also elsewhere on the board
~MRDY~: J5.a27; also elsewhere on the board
~NMI~: J5.c27; also elsewhere on the board
~RD~: J5.a18; also elsewhere on the board
~RESET~: J5.a29; also elsewhere on the board
~WR~: J5.a19; also elsewhere on the board

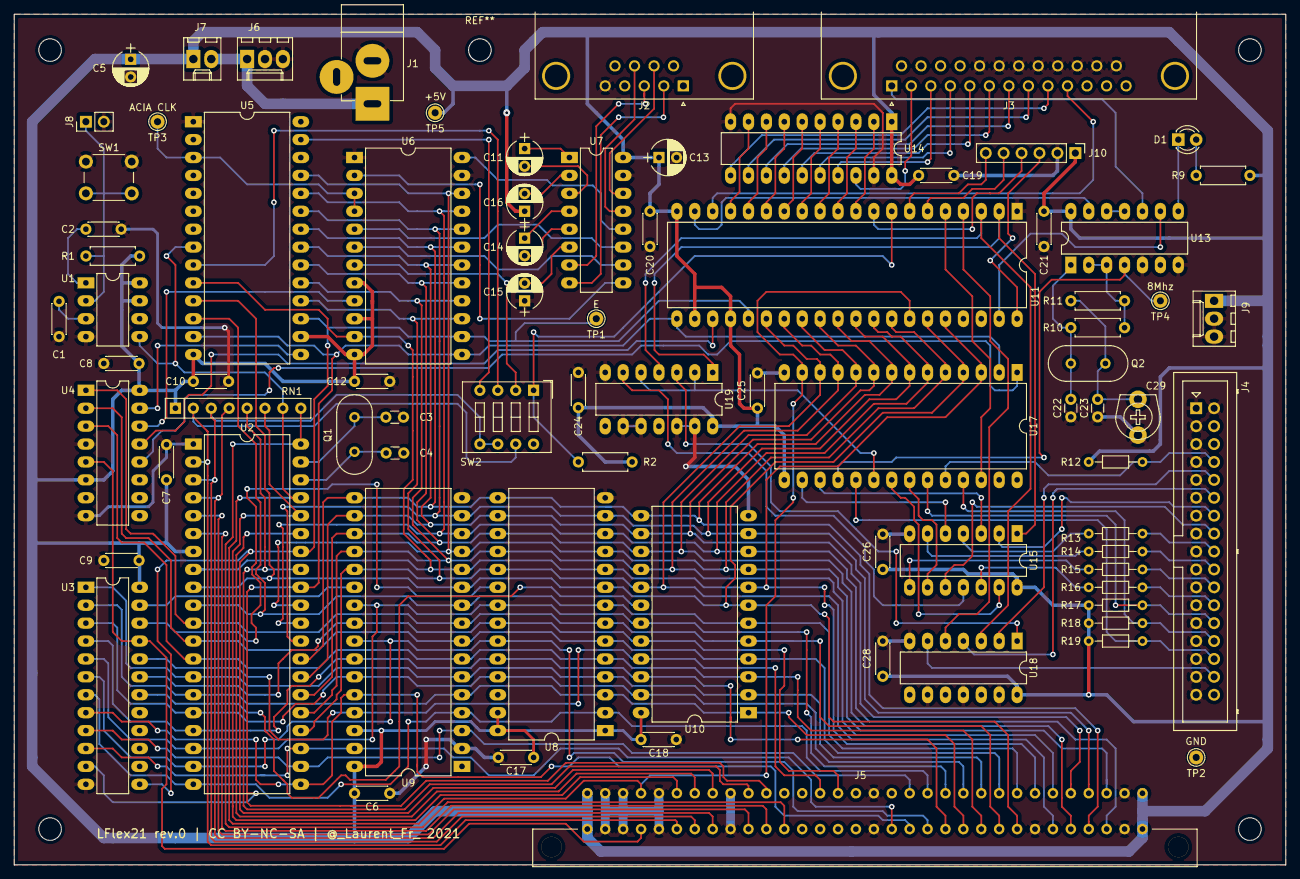
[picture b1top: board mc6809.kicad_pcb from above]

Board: 2 copper layers, 180.3 x 120.6 mm, 79 parts (0 on the bottom side), 132 nets.

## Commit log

2021-08-09 adding README
2021-08-11 Ajout de Assist09
2021-08-16 Adding licence
2021-08-16 Datasheets
2021-08-16 Adding PCB layout
2021-08-18 addig PIA init
2021-08-18 tests
2021-08-18 updating doc
2021-08-18 cleanup
2021-08-18 assist09 LST
2021-08-18 Adding PCB
2021-08-20 Flex disk image
2021-08-25 Flex Adaptation source code
2025-03-05 add newdisk skeletal source from 6809fadg

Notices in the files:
kicad/mc6809.kicad_pcb:
LFlex21 rev.0 | CC BY-NC-SA | @_Laurent_Fr_ 2021
